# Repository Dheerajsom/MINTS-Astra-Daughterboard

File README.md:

# MINTS-Astra-Daughterboard

120 × 80 mm, four-layer EC Sense gas-sensor I2C daughterboard, revision B. The project contains the editable KiCad schematic and PCB, local component libraries, manufacturing files, assembly data, source scripts, reference documents, and verification reports.

## Open the design

Open [`ECSense_4CH_I2C.kicad_pro`](ECSense_4CH_I2C.kicad_pro) in KiCad 10. The project uses local footprint and 3D-model paths. The schematic and board retain their original `ECSense_4CH_I2C` filenames so project references remain intact.

Read [`PCB_README.md`](PCB_README.md) for electrical corrections, connector pinouts, assembly requirements, and bring-up instructions.

## Files

| Location | Contents |
| --- | --- |
| [`ECSense_4CH_I2C.kicad_pcb`](ECSense_4CH_I2C.kicad_pcb) | Completed routed PCB |
| [`ECSense_4CH_I2C.kicad_sch`](ECSense_4CH_I2C.kicad_sch) | Revision B schematic |
| [`ECGAS.pretty/`](ECGAS.pretty), [`libraries/`](libraries), [`models/`](models) | Local footprints and available 3D models |
| [`manufacturing/gerbers/`](manufacturing/gerbers) | Four copper layers, masks, silkscreens, pastes, outline, and drill files |
| [`manufacturing/assembly/`](manufacturing/assembly) | BOM and placement CSVs |
| [`Fabrication and assembly drawings`](output/pdf/Fabrication_and_assembly.pdf) | Mechanical, assembly, and drill drawings |
| [`Schematic PDF`](ECSense_4CH_I2C.pdf) | Printable schematic |
| [`output/`](output) | Board previews and final drawings |
| [`verification/`](verification) | Final checks plus development and routing records |
| [`scripts/`](scripts) | Construction, routing, and export scripts |
| [`sources/`](sources) | Manufacturer reference documents |

Download the [`complete project ZIP`](EC-Sense-120x80-Project.zip) or [`fabrication Gerbers ZIP`](manufacturing/EC-Sense-120x80-Gerbers.zip). The complete project ZIP is the compact release package; this repository also includes supporting development files.

## Verification and fabrication

The final KiCad 10.0.5 checks recorded **0 DRC violations, 0 unconnected items, 0 schematic parity discrepancies, and 0 ERC violations**. See [`final-drc.rpt`](verification/final-drc.rpt), [`final-erc.rpt`](verification/final-erc.rpt), and [`release-summary.json`](verification/release-summary.json). Earlier reports in `verification/` record intermediate work; the `final-*` reports describe the delivered board.

Specify four copper layers, nominal 1.6 mm FR-4, ENIG, and a fabricator supporting **0.075 mm trace/clearance and 0.20 mm via drills with 0.40 mm pads**. Read the full [fabrication notes](manufacturing/FABRICATION_NOTES.txt) before ordering.

This is a hardware prototype. Application firmware, gas-sensor calibration, and physical bench testing are required before use.

## Development records

The saved revision B KiCad project and `PCB_README.md` are authoritative. `DESIGN.md`, the original generator, and intermediate routing files document earlier stages. Construction scripts can overwrite completed routing; review them before running them. Local automatic backups, temporary files, editor state, and caches are ignored by Git.

Third-party KiCad library notices are included in [`libraries/LICENSE.md`](libraries/LICENSE.md) and [`models/kicad/LICENSE.md`](models/kicad/LICENSE.md).

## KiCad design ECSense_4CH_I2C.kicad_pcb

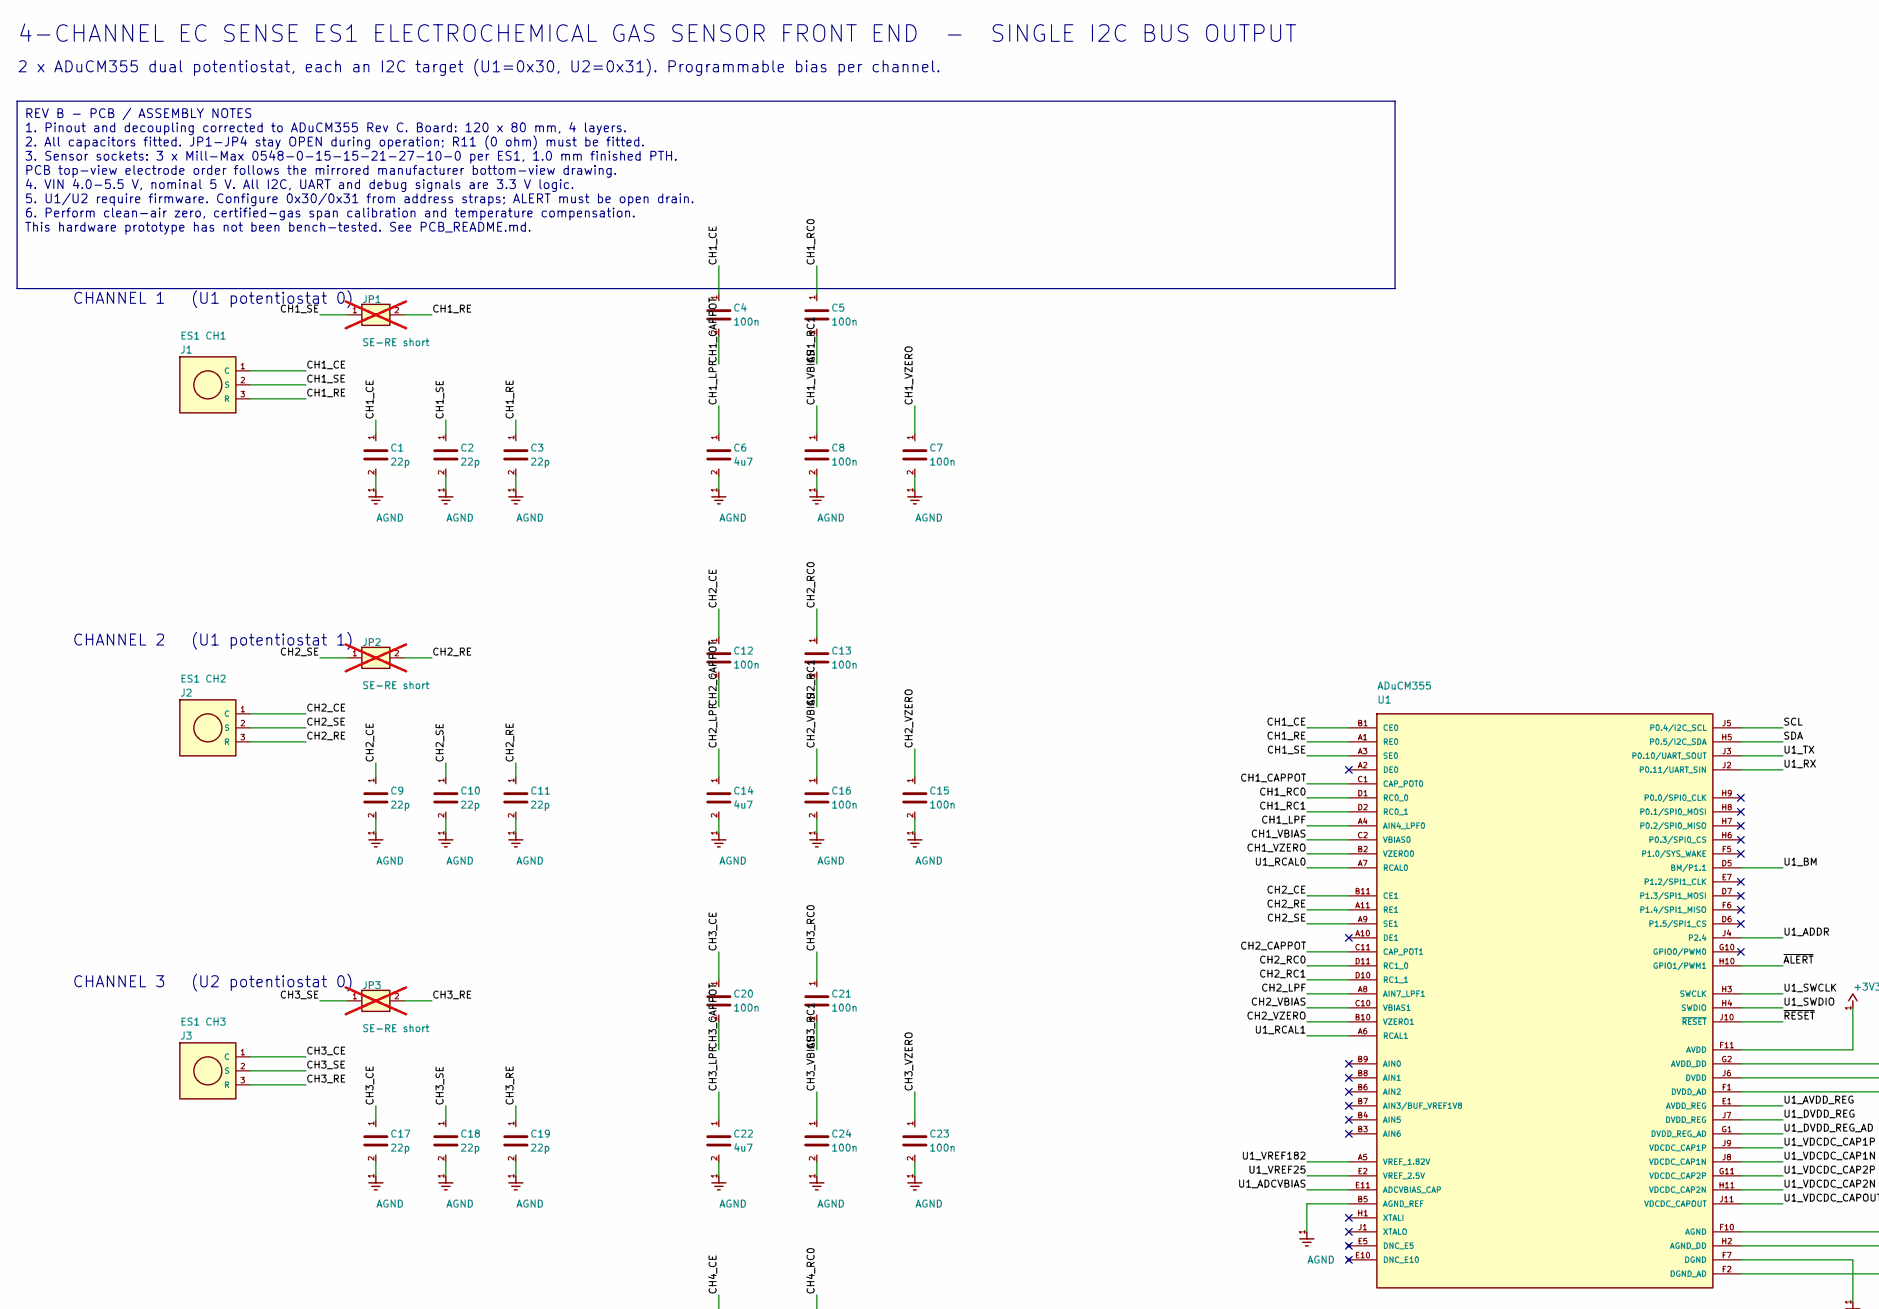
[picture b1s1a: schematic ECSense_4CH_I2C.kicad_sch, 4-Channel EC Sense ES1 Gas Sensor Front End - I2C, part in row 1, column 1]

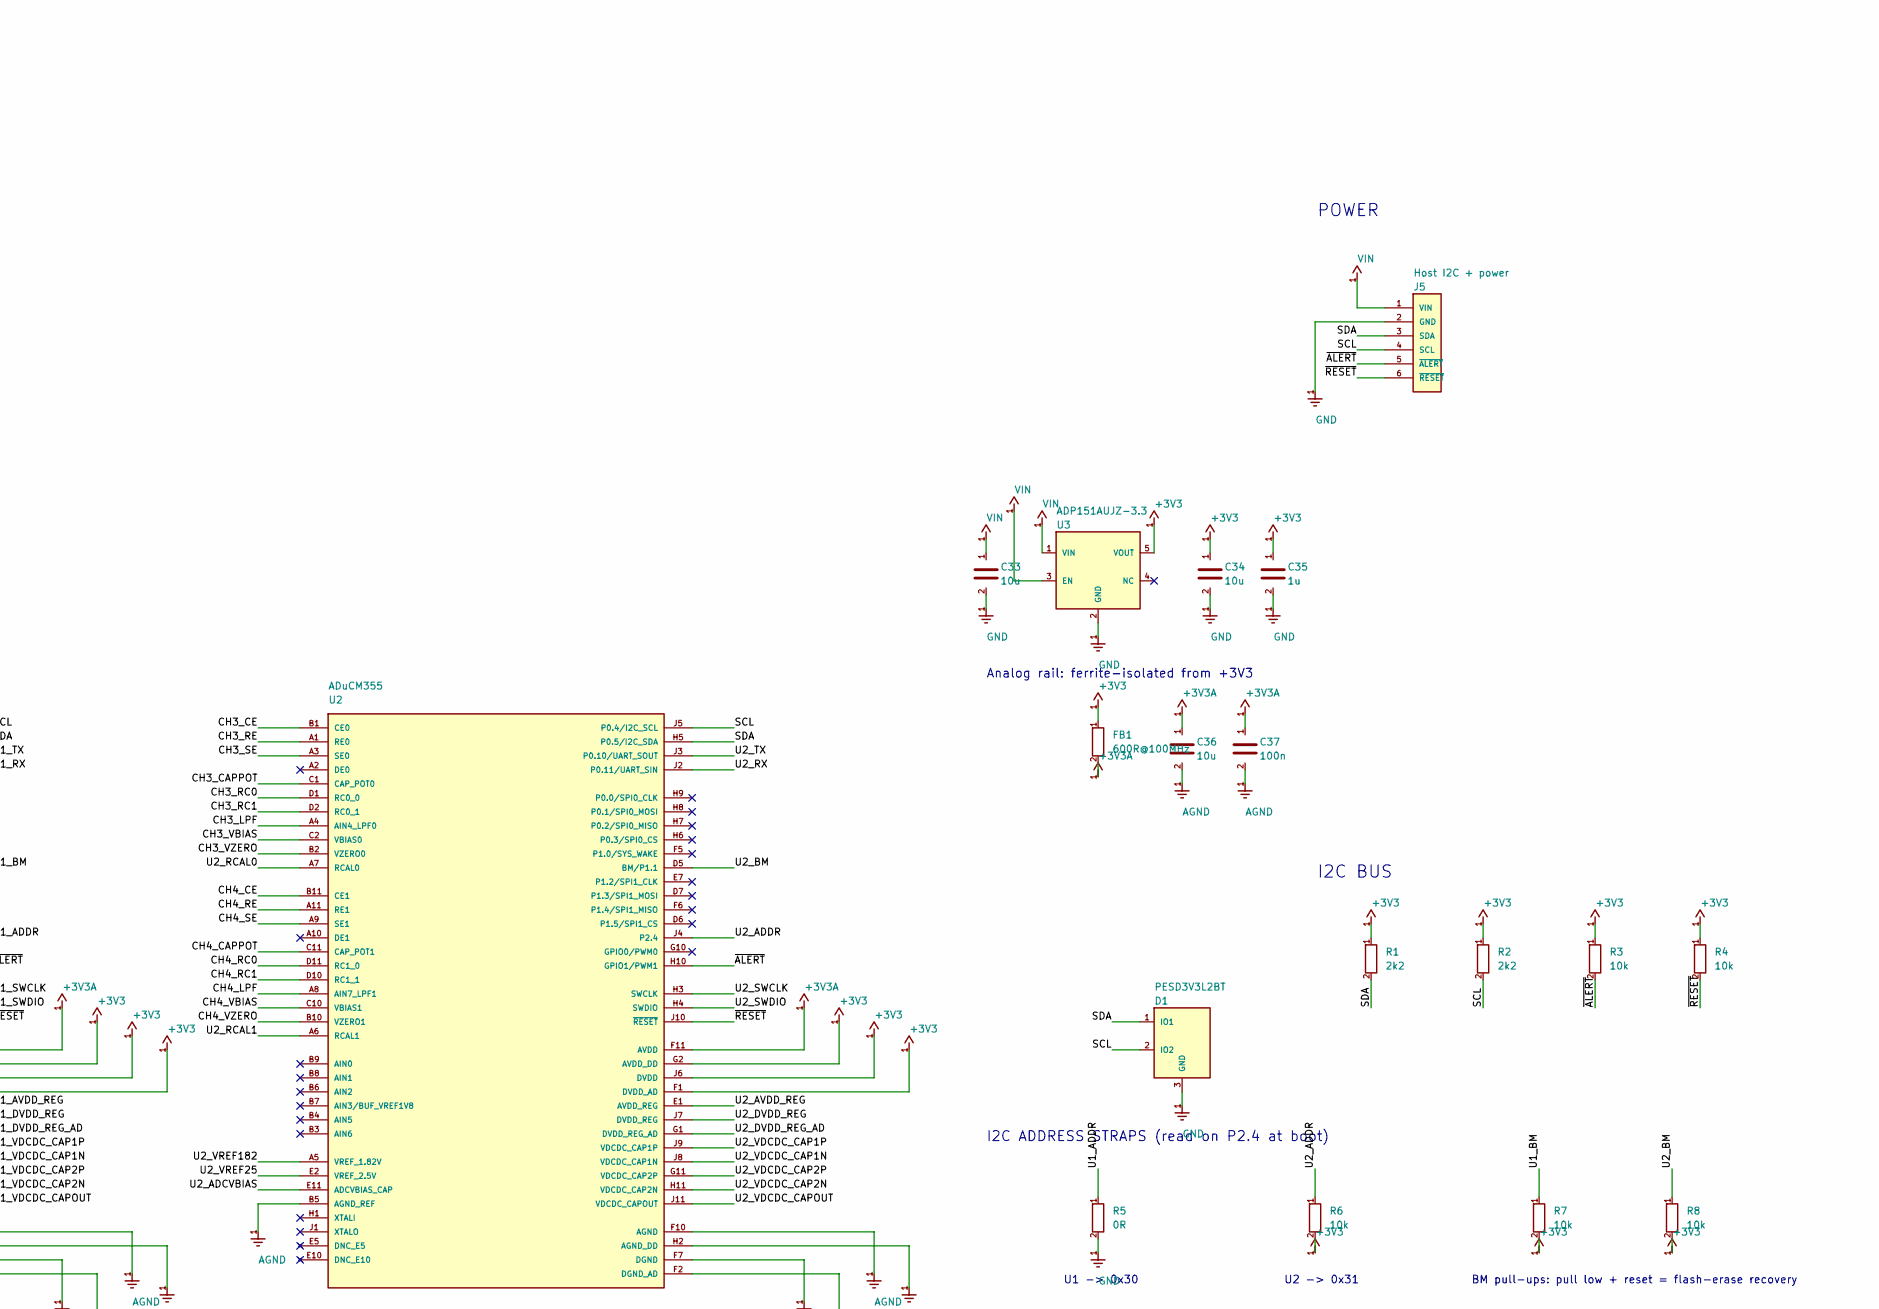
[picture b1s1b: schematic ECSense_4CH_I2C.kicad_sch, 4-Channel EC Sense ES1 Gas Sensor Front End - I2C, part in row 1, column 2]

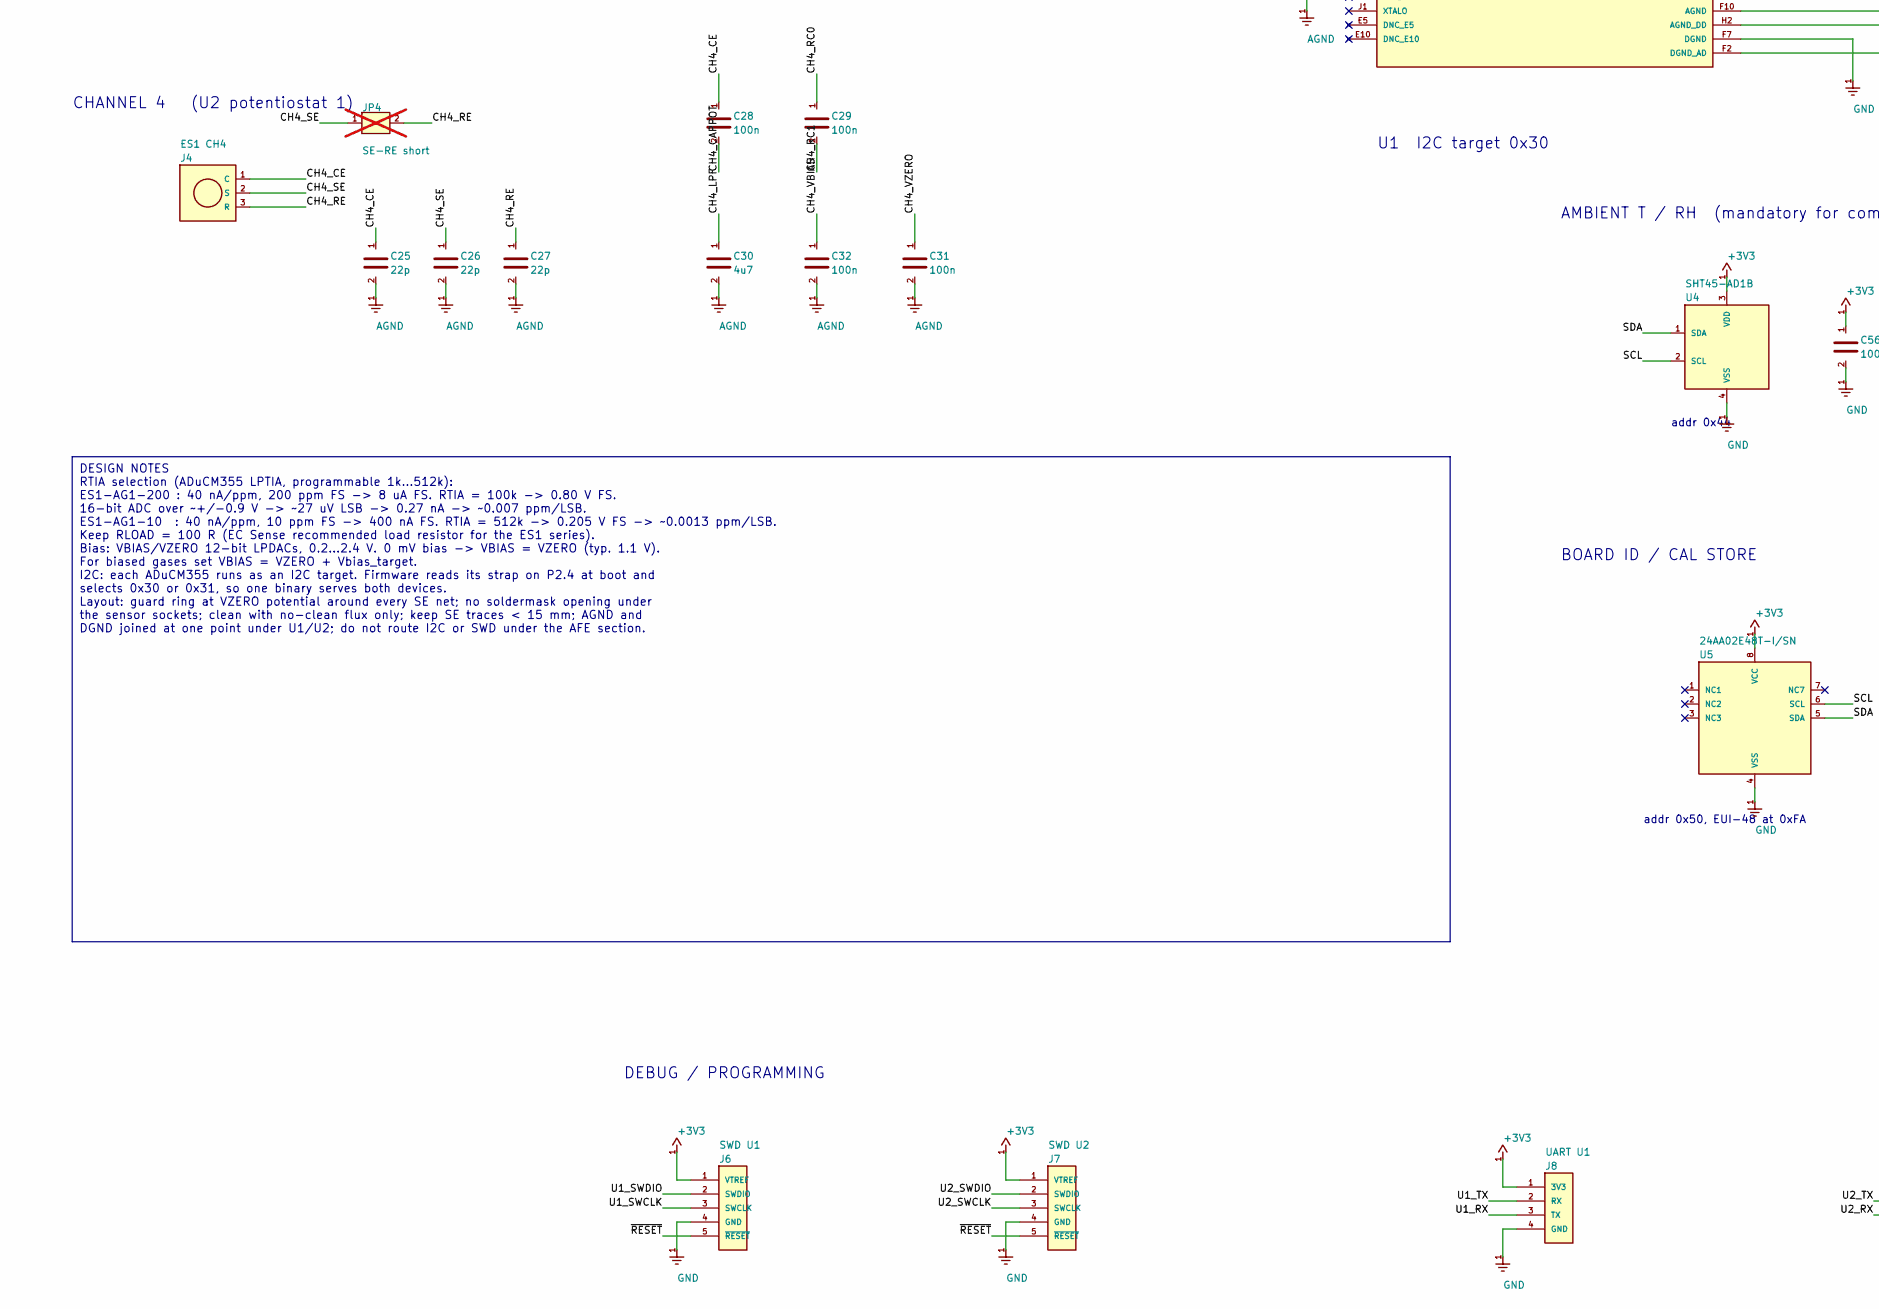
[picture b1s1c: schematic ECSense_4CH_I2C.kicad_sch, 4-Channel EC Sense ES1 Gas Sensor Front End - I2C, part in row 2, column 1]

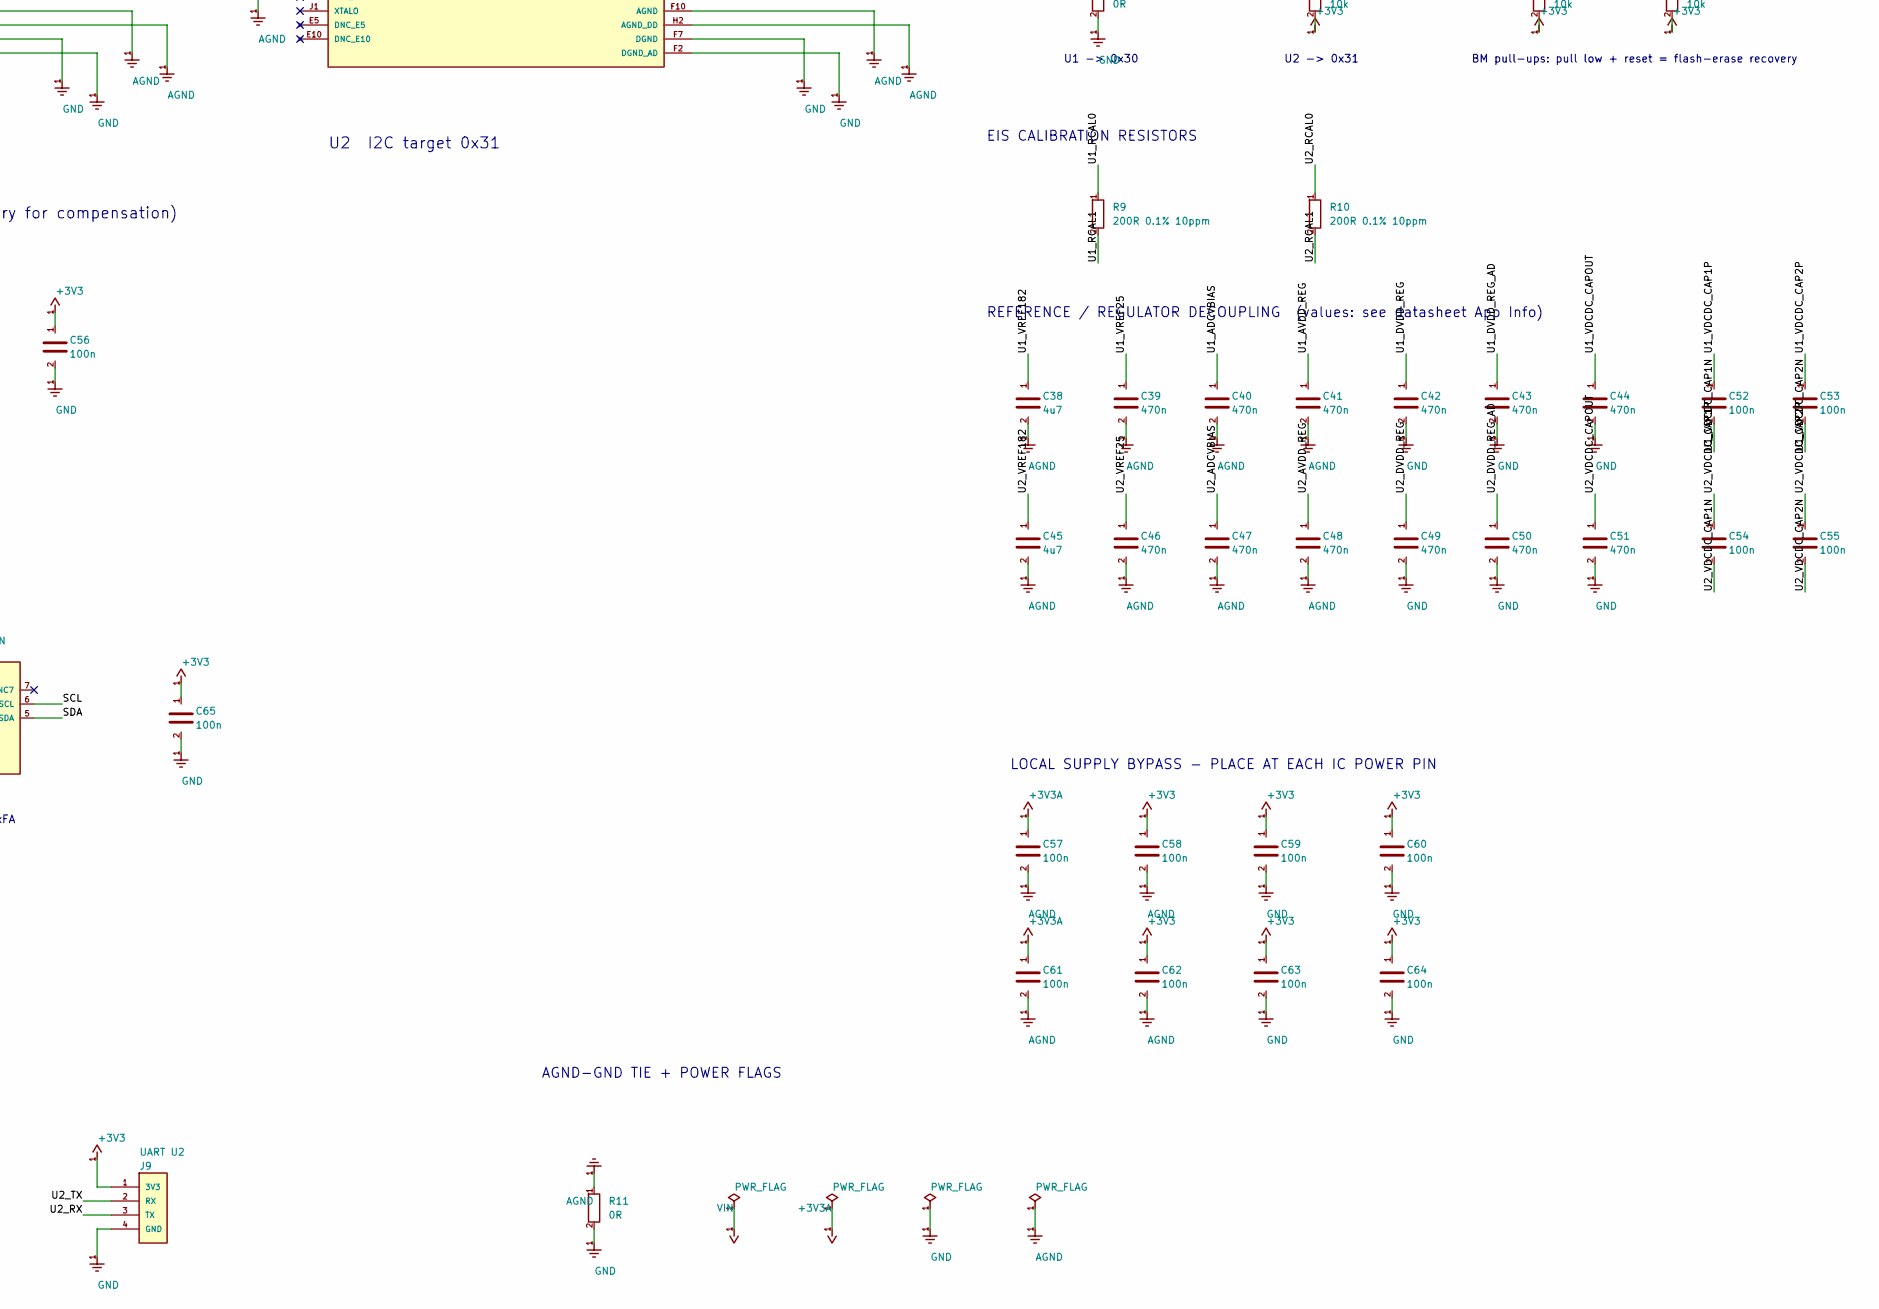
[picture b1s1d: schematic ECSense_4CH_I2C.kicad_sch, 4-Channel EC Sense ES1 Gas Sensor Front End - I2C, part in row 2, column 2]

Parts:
C1, C2, C3, C9, C10, C11, C17, C18, C19, C25, C26, C27: 22p; C_0603_1608Metric
C4, C5, C7, C8, C12, C13, C15, C16, C20, C21, C23, C24, C28, C29, C31, C32, C37, C52, C53, C54, C55, C56, C57, C58, C59, C60, C61, C62, C63, C64, C65: 100n; C_0603_1608Metric
C6, C14, C22, C30, C38, C45: 4u7; C_0603_1608Metric
C33, C34, C36: 10u; C_0603_1608Metric
C35: 1u; C_0603_1608Metric
C39, C40, C41, C42, C43, C44, C46, C47, C48, C49, C50, C51: 470n; C_0603_1608Metric
D1: PESD3V3L2BT; SOT-23
FB1: 600R@100MHz; L_0805_2012Metric
J1: ES1 CH1; EC_Sense_ES1_3pin_2.54mm; MPN 3x Mill-Max 0350 series receptacle (0.3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
J2: ES1 CH2; EC_Sense_ES1_3pin_2.54mm; MPN 3x Mill-Max 0350 series receptacle (0.3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
J3: ES1 CH3; EC_Sense_ES1_3pin_2.54mm; MPN 3x Mill-Max 0350 series receptacle (0.3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
J4: ES1 CH4; EC_Sense_ES1_3pin_2.54mm; MPN 3x Mill-Max 0350 series receptacle (0.3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
J5: Host I2C + power; JST_PH_B6B-PH-K_1x06_P2.00mm_Vertical
J6: SWD U1; PinHeader_1x05_P1.27mm_Vertical
J7: SWD U2; PinHeader_1x05_P1.27mm_Vertical
J8: UART U1; PinHeader_1x04_P2.54mm_Vertical
J9: UART U2; PinHeader_1x04_P2.54mm_Vertical
JP1, JP2, JP3, JP4: SE-RE short; SolderJumper-2_P1.3mm_Open_Pad1.0x1.5mm; not fitted
R1, R2: 2k2; R_0603_1608Metric
R3, R4, R6, R7, R8: 10k; R_0603_1608Metric
R5, R11: 0R; R_0603_1608Metric
R9, R10: 200R 0.1% 10ppm; R_0603_1608Metric
U1, U2: ADuCM355; ADuCM355_LGA-72_6x5mm; MPN ADUCM355BCCZ
U3: ADP151AUJZ-3.3; TSOT-23-5
U4: SHT45-AD1B; Sensirion_DFN-4_1.5x1.5mm_P0.8mm_SHT4x_NoCentralPad
U5: 24AA02E48T-I/SN; SOIC-8_3.9x4.9mm_P1.27mm

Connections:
+3V3: C34.1, C35.1, C56.1, C58.1, C59.1, C60.1, C62.1, C63.1, C64.1, C65.1, FB1.1, J6.1 (VTREF), J7.1 (VTREF), J8.1 (3V3), J9.1 (3V3), R1.1, R2.1, R3.1, R4.1, R6.2, R7.2, R8.2, U1.F1 (DVDD_AD), U1.G2 (AVDD_DD), U1.J6 (DVDD), U2.F1 (DVDD_AD), U2.G2 (AVDD_DD), U2.J6 (DVDD), U3.5 (VOUT), U4.3 (VDD), U5.8 (VCC); also elsewhere on the board
+3V3A: C36.1, C37.1, C57.1, C61.1, FB1.2, U1.F11 (AVDD), U2.F11 (AVDD); also elsewhere on the board
/CH1_CAPPOT: C4.2, U1.C1 (CAP_POT0)
/CH1_CE: C1.1, C4.1, J1.1 (C), U1.B1 (CE0)
/CH1_LPF: C6.1, U1.A4 (AIN4_LPF0)
/CH1_RC0: C5.1, U1.D1 (RC0_0)
/CH1_RC1: C5.2, U1.D2 (RC0_1)
/CH1_RE: C3.1, J1.3 (R), JP1.2 (B), U1.A1 (RE0)
/CH1_SE: C2.1, J1.2 (S), JP1.1 (A), U1.A3 (SE0)
/CH1_VBIAS: C8.1, U1.C2 (VBIAS0)
/CH1_VZERO: C7.1, U1.B2 (VZERO0)
/CH2_CAPPOT: C12.2, U1.C11 (CAP_POT1)
/CH2_CE: C9.1, C12.1, J2.1 (C), U1.B11 (CE1)
/CH2_LPF: C14.1, U1.A8 (AIN7_LPF1)
/CH2_RC0: C13.1, U1.D11 (RC1_0)
/CH2_RC1: C13.2, U1.D10 (RC1_1)
/CH2_RE: C11.1, J2.3 (R), JP2.2 (B), U1.A11 (RE1)
/CH2_SE: C10.1, J2.2 (S), JP2.1 (A), U1.A9 (SE1)
/CH2_VBIAS: C16.1, U1.C10 (VBIAS1)
/CH2_VZERO: C15.1, U1.B10 (VZERO1)
/CH3_CAPPOT: C20.2, U2.C1 (CAP_POT0)
/CH3_CE: C17.1, C20.1, J3.1 (C), U2.B1 (CE0)
/CH3_LPF: C22.1, U2.A4 (AIN4_LPF0)
/CH3_RC0: C21.1, U2.D1 (RC0_0)
/CH3_RC1: C21.2, U2.D2 (RC0_1)
/CH3_RE: C19.1, J3.3 (R), JP3.2 (B), U2.A1 (RE0)
/CH3_SE: C18.1, J3.2 (S), JP3.1 (A), U2.A3 (SE0)
/CH3_VBIAS: C24.1, U2.C2 (VBIAS0)
/CH3_VZERO: C23.1, U2.B2 (VZERO0)
/CH4_CAPPOT: C28.2, U2.C11 (CAP_POT1)
/CH4_CE: C25.1, C28.1, J4.1 (C), U2.B11 (CE1)
/CH4_LPF: C30.1, U2.A8 (AIN7_LPF1)
/CH4_RC0: C29.1, U2.D11 (RC1_0)
/CH4_RC1: C29.2, U2.D10 (RC1_1)
/CH4_RE: C27.1, J4.3 (R), JP4.2 (B), U2.A11 (RE1)
/CH4_SE: C26.1, J4.2 (S), JP4.1 (A), U2.A9 (SE1)
/CH4_VBIAS: C32.1, U2.C10 (VBIAS1)
/CH4_VZERO: C31.1, U2.B10 (VZERO1)
/SCL: D1.2 (IO2), J5.4 (SCL), R2.2, U1.J5 (P0.4/I2C_SCL), U2.J5 (P0.4/I2C_SCL), U4.2 (SCL), U5.6 (SCL); also elsewhere on the board
/SDA: D1.1 (IO1), J5.3 (SDA), R1.2, U1.H5 (P0.5/I2C_SDA), U2.H5 (P0.5/I2C_SDA), U4.1 (SDA), U5.5 (SDA); also elsewhere on the board
/U1_ADCVBIAS: C40.1, U1.E11 (ADCVBIAS_CAP)
/U1_ADDR: R5.1, U1.J4 (P2.4)
/U1_AVDD_REG: C41.1, U1.E1 (AVDD_REG)
/U1_BM: R7.1, U1.D5 (BM/P1.1); also elsewhere on the board
/U1_DVDD_REG: C42.1, U1.J7 (DVDD_REG)
/U1_DVDD_REG_AD: C43.1, U1.G1 (DVDD_REG_AD)
/U1_RCAL0: R9.1, U1.A7 (RCAL0)
/U1_RCAL1: R9.2, U1.A6 (RCAL1)
/U1_RX: J8.3 (TX), U1.J2 (P0.11/UART_SIN)
/U1_SWCLK: J6.3 (SWCLK), U1.H3 (SWCLK)
/U1_SWDIO: J6.2 (SWDIO), U1.H4 (SWDIO)
/U1_TX: J8.2 (RX), U1.J3 (P0.10/UART_SOUT)
/U1_VDCDC_CAP1N: C52.2, U1.J8 (VDCDC_CAP1N)
/U1_VDCDC_CAP1P: C52.1, U1.J9 (VDCDC_CAP1P)
/U1_VDCDC_CAP2N: C53.2, U1.H11 (VDCDC_CAP2N)
/U1_VDCDC_CAP2P: C53.1, U1.G11 (VDCDC_CAP2P)
/U1_VDCDC_CAPOUT: C44.1, U1.J11 (VDCDC_CAPOUT)
/U1_VREF25: C39.1, U1.E2 (VREF_2.5V)
/U1_VREF182: C38.1, U1.A5 (VREF_1.82V)
/U2_ADCVBIAS: C47.1, U2.E11 (ADCVBIAS_CAP)
/U2_ADDR: R6.1, U2.J4 (P2.4)
/U2_AVDD_REG: C48.1, U2.E1 (AVDD_REG)
/U2_BM: R8.1, U2.D5 (BM/P1.1); also elsewhere on the board
/U2_DVDD_REG: C49.1, U2.J7 (DVDD_REG)
/U2_DVDD_REG_AD: C50.1, U2.G1 (DVDD_REG_AD)
/U2_RCAL0: R10.1, U2.A7 (RCAL0)
/U2_RCAL1: R10.2, U2.A6 (RCAL1)
/U2_RX: J9.3 (TX), U2.J2 (P0.11/UART_SIN)
/U2_SWCLK: J7.3 (SWCLK), U2.H3 (SWCLK)
/U2_SWDIO: J7.2 (SWDIO), U2.H4 (SWDIO)
/U2_TX: J9.2 (RX), U2.J3 (P0.10/UART_SOUT)
/U2_VDCDC_CAP1N: C54.2, U2.J8 (VDCDC_CAP1N)
/U2_VDCDC_CAP1P: C54.1, U2.J9 (VDCDC_CAP1P)
/U2_VDCDC_CAP2N: C55.2, U2.H11 (VDCDC_CAP2N)
/U2_VDCDC_CAP2P: C55.1, U2.G11 (VDCDC_CAP2P)
/U2_VDCDC_CAPOUT: C51.1, U2.J11 (VDCDC_CAPOUT)
/U2_VREF25: C46.1, U2.E2 (VREF_2.5V)
/U2_VREF182: C45.1, U2.A5 (VREF_1.82V)
/~ALERT: J5.5 (~ALERT), R3.2, U1.H10 (GPIO1/PWM1), U2.H10 (GPIO1/PWM1)
/~RESET: J5.6 (~RESET), J6.5 (~RESET), J7.5 (~RESET), R4.2, U1.J10 (~RESET), U2.J10 (~RESET)
AGND: C1.2, C2.2, C3.2, C6.2, C7.2, C8.2, C9.2, C10.2, C11.2, C14.2, C15.2, C16.2, C17.2, C18.2, C19.2, C22.2, C23.2, C24.2, C25.2, C26.2, C27.2, C30.2, C31.2, C32.2, C36.2, C37.2, C38.2, C39.2, C40.2, C41.2, C45.2, C46.2, C47.2, C48.2, C57.2, C58.2, C61.2, C62.2, R11.1, U1.B5 (AGND_REF), U1.F10 (AGND), U1.H2 (AGND_DD), U2.B5 (AGND_REF), U2.F10 (AGND), U2.H2 (AGND_DD); also elsewhere on the board
GND: C33.2, C34.2, C35.2, C42.2, C43.2, C44.2, C49.2, C50.2, C51.2, C56.2, C59.2, C60.2, C63.2, C64.2, C65.2, D1.3 (GND), J5.2 (GND), J6.4 (GND), J7.4 (GND), J8.4 (GND), J9.4 (GND), R5.2, R11.2, U1.F2 (DGND_AD), U1.F7 (DGND), U2.F2 (DGND_AD), U2.F7 (DGND), U3.2 (GND), U4.4 (VSS), U5.4 (VSS); also elsewhere on the board
VIN: C33.1, J5.1 (VIN), U3.1 (VIN), U3.3 (EN); also elsewhere on the board

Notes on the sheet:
EIS CALIBRATION RESISTORS
CHANNEL 1 (U1 potentiostat 0)
AGND-GND TIE + POWER FLAGS
addr 0x44
CHANNEL 3 (U2 potentiostat 0)
U2 I2C target 0x31
addr 0x50, EUI-48 at 0xFA
4-CHANNEL EC SENSE ES1 ELECTROCHEMICAL GAS SENSOR FRONT END - SINGLE I2C BUS OUTPUT
U1 -> 0x30
DEBUG / PROGRAMMING
Analog rail: ferrite-isolated from +3V3
U2 -> 0x31
BM pull-ups: pull low + reset = flash-erase recovery
AMBIENT T / RH (mandatory for compensation)
REFERENCE / REGULATOR DECOUPLING (values: see datasheet App Info)
POWER
BOARD ID / CAL STORE
2 x ADuCM355 dual potentiostat, each an I2C target (U1=0x30, U2=0x31). Programmable bias per channel.
LOCAL SUPPLY BYPASS - PLACE AT EACH IC POWER PIN
I2C ADDRESS STRAPS (read on P2.4 at boot)
CHANNEL 2 (U1 potentiostat 1)
CHANNEL 4 (U2 potentiostat 1)
U1 I2C target 0x30
I2C BUS
REV B - PCB / ASSEMBLY NOTES 1. Pinout and decoupling corrected to ADuCM355 Rev C. Board: 120 x 80 mm, 4 layers. 2. All capacitors fitted. JP1-JP4 stay OPEN during operation; R11 (0 ohm) must be fitted. 3. Sensor sockets: 3 x Mill-Max 0548-0-15-15-21-27-10-0 per ES1, 1.0 mm finished PTH. PCB top-vi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
DESIGN NOTES RTIA selection (ADuCM355 LPTIA, programmable 1k...512k): ES1-AG1-200 : 40 nA/ppm, 200 ppm FS -> 8 uA FS. RTIA = 100k -> 0.80 V FS. 16-bit ADC over ~+/-0.9 V -> ~27 uV LSB -> 0.27 nA -> ~0.007 ppm/LSB. ES1-AG1-10 : 40 nA/ppm, 10 ppm FS -> 400 nA FS. RTIA = 512k -> 0.205 V FS -> ~0.0013 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

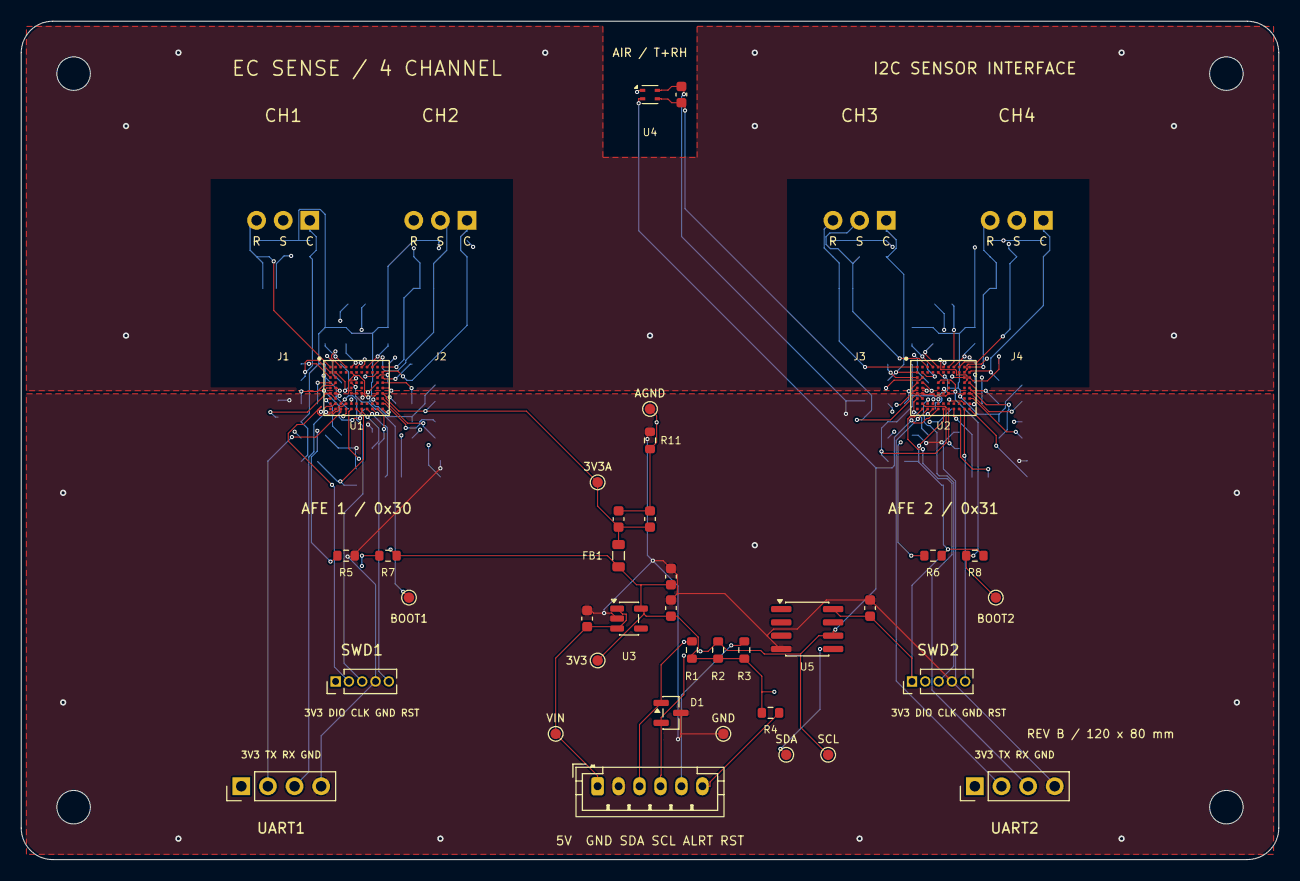
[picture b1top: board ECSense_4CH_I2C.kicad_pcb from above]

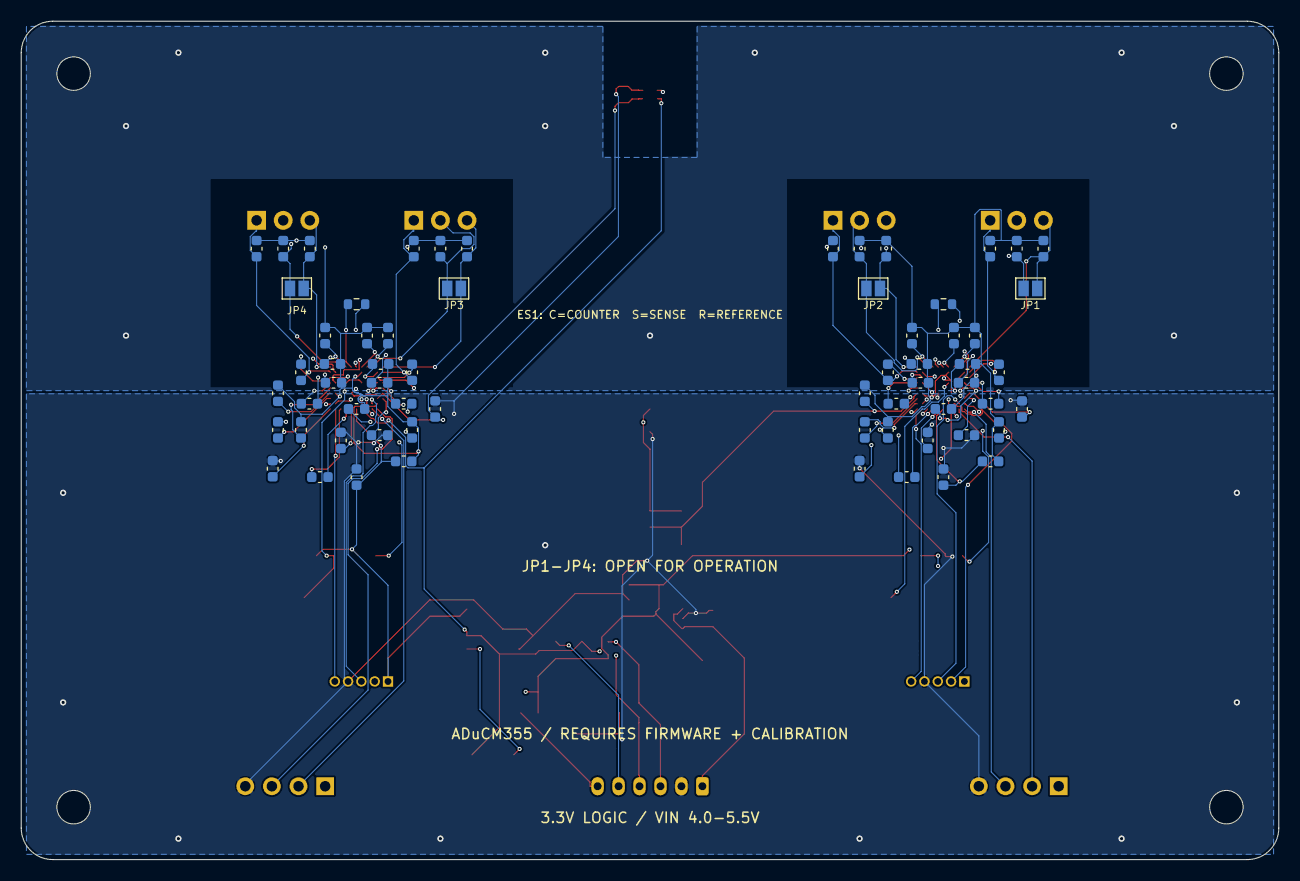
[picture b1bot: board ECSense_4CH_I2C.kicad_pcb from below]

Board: 4 copper layers, 120.0 x 80.0 mm, 109 parts (64 on the bottom side), 83 nets.

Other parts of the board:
H1, H2, H3, H4: M3; MountingHole_3.2mm_M3
TP1: VIN; TestPoint_Pad_D1.0mm
TP2: 3V3; TestPoint_Pad_D1.0mm
TP3: 3V3A; TestPoint_Pad_D1.0mm
TP4: GND; TestPoint_Pad_D1.0mm
TP5: AGND; TestPoint_Pad_D1.0mm
TP6: BOOT1; TestPoint_Pad_D1.0mm
TP7: BOOT2; TestPoint_Pad_D1.0mm
TP8: SDA; TestPoint_Pad_D1.0mm
TP9: SCL; TestPoint_Pad_D1.0mm

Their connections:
+3V3: TP2.1; also elsewhere on the board
+3V3A: TP3.1; also elsewhere on the board
/SCL: TP9.1; also elsewhere on the board
/SDA: TP8.1; also elsewhere on the board
/U1_BM: TP6.1; also elsewhere on the board
/U2_BM: TP7.1; also elsewhere on the board
AGND: TP5.1; also elsewhere on the board
GND: TP4.1; also elsewhere on the board
VIN: TP1.1; also elsewhere on the board

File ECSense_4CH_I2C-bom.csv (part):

"References","Value","Footprint","Quantity","DNP","Manufacturer_Part","Tolerance","Assembly_Note"
"C1","22p","Capacitor_SMD:C_0603_1608Metric","1","","","C0G 5%","EMC filter, keep at socket"
"C2","22p","Capacitor_SMD:C_0603_1608Metric","1","","","C0G 5%","EMC filter, keep at socket"
"C3","22p","Capacitor_SMD:C_0603_1608Metric","1","","","C0G 5%","EMC filter, keep at socket"
"C4","100n","Capacitor_SMD:C_0603_1608Metric","1","","","","Potentiostat loop compensation, CE to CAP_POT"
"C5","100n","Capacitor_SMD:C_0603_1608Metric","1","","","","LPTIA RC filter between RCx_0 and RCx_1"
"C6","4u7","Capacitor_SMD:C_0603_1608Metric","1","","","","LPTIA output low-pass, X7R 10V"
"C7","100n","Capacitor_SMD:C_0603_1608Metric","1","","","","Required VZERO decoupling per ADuCM355 Rev C p26"
"C8","100n","Capacitor_SMD:C_0603_1608Metric","1","","","","VBIAS decoupling"
"C9","22p","Capacitor_SMD:C_0603_1608Metric","1","","","C0G 5%","EMC filter, keep at socket"
"C10","22p","Capacitor_SMD:C_0603_1608Metric","1","","","C0G 5%","EMC filter, keep at socket"
"C11","22p","Capacitor_SMD:C_0603_1608Metric","1","","","C0G 5%","EMC filter, keep at socket"
"C12","100n","Capacitor_SMD:C_0603_1608Metric","1","","","","Potentiostat loop compensation, CE to CAP_POT"
"C13","100n","Capacitor_SMD:C_0603_1608Metric","1","","","","LPTIA RC filter between RCx_0 and RCx_1"
"C14","4u7","Capacitor_SMD:C_0603_1608Metric","1","","","","LPTIA output low-pass, X7R 10V"
"C15","100n","Capacitor_SMD:C_0603_1608Metric","1","","","","Required VZERO decoupling per ADuCM355 Rev C p26"
"C16","100n","Capacitor_SMD:C_0603_1608Metric","1","","","","VBIAS decoupling"
"C17","22p","Capacitor_SMD:C_0603_1608Metric","1","","","C0G 5%","EMC filter, keep at socket"
"C18","22p","Capacitor_SMD:C_0603_1608Metric","1","","","C0G 5%","EMC filter, keep at socket"
"C19","22p","Capacitor_SMD:C_0603_1608Metric","1","","","C0G 5%","EMC filter, keep at socket"
"C20","100n","Capacitor_SMD:C_0603_1608Metric","1","","","","Potentiostat loop compensation, CE to CAP_POT"
"C21","100n","Capacitor_SMD:C_0603_1608Metric","1","","","","LPTIA RC filter between RCx_0 and RCx_1"
"C22","4u7","Capacitor_SMD:C_0603_1608Metric","1","","","","LPTIA output low-pass, X7R 10V"
"C23","100n","Capacitor_SMD:C_0603_1608Metric","1","","","","Required VZERO decoupling per ADuCM355 Rev C p26"
"C24","100n","Capacitor_SMD:C_0603_1608Metric","1","","","","VBIAS decoupling"
"C25","22p","Capacitor_SMD:C_0603_1608Metric","1","","","C0G 5%","EMC filter, keep at socket"
"C26","22p","Capacitor_SMD:C_0603_1608Metric","1","","","C0G 5%","EMC filter, keep at socket"
"C27","22p","Capacitor_SMD:C_0603_1608Metric","1","","","C0G 5%","EMC filter, keep at socket"
"C28","100n","Capacitor_SMD:C_0603_1608Metric","1","","","","Potentiostat loop compensation, CE to CAP_POT"
"C29","100n","Capacitor_SMD:C_0603_1608Metric","1","","","","LPTIA RC filter between RCx_0 and RCx_1"
"C30","4u7","Capacitor_SMD:C_0603_1608Metric","1","","","","LPTIA output low-pass, X7R 10V"
"C31","100n","Capacitor_SMD:C_0603_1608Metric","1","","","","Required VZERO decoupling per ADuCM355 Rev C p26"
"C32","100n","Capacitor_SMD:C_0603_1608Metric","1","","","","VBIAS decoupling"
"C33","10u","Capacitor_SMD:C_0603_1608Metric","1","","","",""
"C34","10u","Capacitor_SMD:C_0603_1608Metric","1","","","",""
"C35","1u","Capacitor_SMD:C_0603_1608Metric","1","","","",""
"C36","10u","Capacitor_SMD:C_0603_1608Metric","1","","","",""
"C37","100n","Capacitor_SMD:C_0603_1608Metric","1","","","",""
"C38","4u7","Capacitor_SMD:C_0603_1608Metric","1","","","",""
"C39","470n","Capacitor_SMD:C_0603_1608Metric","1","","","",""
"C40","470n","Capacitor_SMD:C_0603_1608Metric","1","","","",""
"C41","470n","Capacitor_SMD:C_0603_1608Metric","1","","","",""
"C42","470n","Capacitor_SMD:C_0603_1608Metric","1","","","",""
"C43","470n","Capacitor_SMD:C_0603_1608Metric","1","","","",""
"C44","470n","Capacitor_SMD:C_0603_1608Metric","1","","","",""
"C45","4u7","Capacitor_SMD:C_0603_1608Metric","1","","","",""
"C46","470n","Capacitor_SMD:C_0603_1608Metric","1","","","",""
"C47","470n","Capacitor_SMD:C_0603_1608Metric","1","","","",""
"C48","470n","Capacitor_SMD:C_0603_1608Metric","1","","","",""
"C49","470n","Capacitor_SMD:C_0603_1608Metric","1","","","",""
"C50","470n","Capacitor_SMD:C_0603_1608Metric","1","","","",""
"C51","470n","Capacitor_SMD:C_0603_1608Metric","1","","","",""
"C52","100n","Capacitor_SMD:C_0603_1608Metric","1","","","",""
"C53","100n","Capacitor_SMD:C_0603_1608Metric","1","","","",""
"C54","100n","Capacitor_SMD:C_0603_1608Metric","1","","","",""
"C55","100n","Capacitor_SMD:C_0603_1608Metric","1","","","",""
"C56","100n","Capacitor_SMD:C_0603_1608Metric","1","","","",""
"C57","100n","Capacitor_SMD:C_0603_1608Metric","1","","","","U1 AVDD local bypass"
"C58","100n","Capacitor_SMD:C_0603_1608Metric","1","","","","U1 AVDD_DD local bypass"
"C59","100n","Capacitor_SMD:C_0603_1608Metric","1","","","","U1 DVDD local bypass"
"C60","100n","Capacitor_SMD:C_0603_1608Metric","1","","","","U1 DVDD_AD local bypass"
"C61","100n","Capacitor_SMD:C_0603_1608Metric","1","","","","U2 AVDD local bypass"
"C62","100n","Capacitor_SMD:C_0603_1608Metric","1","","","","U2 AVDD_DD local bypass"
"C63","100n","Capacitor_SMD:C_0603_1608Metric","1","","","","U2 DVDD local bypass"
"C64","100n","Capacitor_SMD:C_0603_1608Metric","1","","","","U2 DVDD_AD local bypass"
"C65","100n","Capacitor_SMD:C_0603_1608Metric","1","","","","U5 local bypass"
"D1","PESD3V3L2BT","Package_TO_SOT_SMD:SOT-23","1","","","",""
"FB1","600R@100MHz","Inductor_SMD:L_0805_2012Metric","1","","","",""
"J1","ES1 CH1","ECGAS:EC_Sense_ES1_3pin_2.54mm","1","","3x Mill-Max 0350 series receptacle (0.30-0.51 mm pin)","","EC Sense ES1 bare sensor, C/S/R, 2.54 mm pitch"
"J2","ES1 CH2","ECGAS:EC_Sense_ES1_3pin_2.54mm","1","","3x Mill-Max 0350 series receptacle (0.30-0.51 mm pin)","","EC Sense ES1 bare sensor, C/S/R, 2.54 mm pitch"
"J3","ES1 CH3","ECGAS:EC_Sense_ES1_3pin_2.54mm","1","","3x Mill-Max 0350 series receptacle (0.30-0.51 mm pin)","","EC Sense ES1 bare sensor, C/S/R, 2.54 mm pitch"
"J4","ES1 CH4","ECGAS:EC_Sense_ES1_3pin_2.54mm","1","","3x Mill-Max 0350 series receptacle (0.30-0.51 mm pin)","","EC Sense ES1 bare sensor, C/S/R, 2.54 mm pitch"
"J5","Host I2C + power","Connector_JST:JST_PH_B6B-PH-K_1x06_P2.00mm_Vertical","1","","","","VIN 4.0-5.5 V; nominal 5 V"
"J6","SWD U1","Connector_PinHeader_1.27mm:PinHeader_1x05_P1.27mm_Vertical","1","","","",""
"J7","SWD U2","Connector_PinHeader_1.27mm:PinHeader_1x05_P1.27mm_Vertical","1","","","",""
"J8","UART U1","Connector_PinHeader_2.54mm:PinHeader_1x04_P2.54mm_Vertical","1","","","",""
"J9","UART U2","Connector_PinHeader_2.54mm:PinHeader_1x04_P2.54mm_Vertical","1","","","",""
"JP1","SE-RE short","Jumper:SolderJumper-2_P1.3mm_Open_Pad1.0x1.5mm","1","DNP","","","Fit only for storage/transport. Remove before measurement."
"JP2","SE-RE short","Jumper:SolderJumper-2_P1.3mm_Open_Pad1.0x1.5mm","1","DNP","","","Fit only for storage/transport. Remove before measurement."
"JP3","SE-RE short","Jumper:SolderJumper-2_P1.3mm_Open_Pad1.0x1.5mm","1","DNP","","","Fit only for storage/transport. Remove before measurement."
"JP4","SE-RE short","Jumper:SolderJumper-2_P1.3mm_Open_Pad1.0x1.5mm","1","DNP","","","Fit only for storage/transport. Remove before measurement."
"R1","2k2","Resistor_SMD:R_0603_1608Metric","1","","","",""
"R2","2k2","Resistor_SMD:R_0603_1608Metric","1","","","",""
"R3","10k","Resistor_SMD:R_0603_1608Metric","1","","","",""
"R4","10k","Resistor_SMD:R_0603_1608Metric","1","","","",""
"R5","0R","Resistor_SMD:R_0603_1608Metric","1","","","",""
"R6","10k","Resistor_SMD:R_0603_1608Metric","1","","","",""
"R7","10k","Resistor_SMD:R_0603_1608Metric","1","","","",""
"R8","10k","Resistor_SMD:R_0603_1608Metric","1","","","",""
"R9","200R 0.1% 10ppm","Resistor_SMD:R_0603_1608Metric","1","","","","RCAL between RCAL0 and RCAL1, low tempco"
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
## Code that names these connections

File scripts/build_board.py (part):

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for i,(x,y) in enumerate([(55,55),(165,55),(55,125),(165,125)],1):
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# Test pads - independent of schematic, same-net copper access.
for i,(name,x,y,label) in enumerate([('VIN',101,118,'VIN'),('+3V3',105,111,'3V3'),('+3V3A',105,94,'3V3A'),('GND',117,118,'GND'),('AGND',110,87,'AGND'),('/U1_BM',87,105,'BOOT1'),('/U2_BM',143,105,'BOOT2'),('/SDA',123,120,'SDA'),('/SCL',127,120,'SCL')],1):
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 for pad in f.Pads():pad.SetNet(netobjs[name])
# Outline with 3 mm corner radii, exact outside dimensions 120 x 80 mm.
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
